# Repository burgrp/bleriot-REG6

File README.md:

# BleRiot REG6

REG6 is a six-channel solid-state-relay controller built around a
PY32F030 and PAN2110. This repository contains the KiCad hardware and a
standalone TinyGo/BleRiot module under `fw/` that exposes one integer percentage
for each channel.

## Hardware

The firmware targets a PY32F030x8 at 24 MHz. TIM1 and TIM3 generate all six
PWM outputs in hardware at a common 24 kHz frequency. Each analog path uses a
loaded two-stage 1.5 kOhm/100 nF RC ladder, whose poles are approximately
405 Hz and 2.78 kHz, followed by an LM358 with a nominal gain of 1.56. At 50%
duty, the ideal nominal filter model predicts about 12 mV peak-to-peak ripple
at 24 kHz, compared with about 2.56 V peak-to-peak at 1 kHz. The PAN2110 uses the
BleRiot three-wire SPI driver, and six chained WS2812B LEDs report channel and
link state.

| Function | MCU pin | Peripheral | Alternate function |
|---|---|---|---:|
| PWM channel 1 | PA8 | TIM1_CH1 | AF2 |
| PWM channel 2 | PA9 | TIM1_CH2 | AF2 |
| PWM channel 3 | PA10 | TIM1_CH3 | AF2 |
| PWM channel 4 | PB4 | TIM3_CH1 | AF1 |
| PWM channel 5 | PB5 | TIM3_CH2 | AF1 |
| PWM channel 6 | PF3 | TIM3_CH3 | AF13 |
| PAN2110 CSN | PF1 | GPIO | - |
| PAN2110 SCK | PA2 | GPIO, bit-banged SPI | - |
| PAN2110 DATA | PA3 | GPIO, bidirectional SPI | - |
| WS2812B data, D1-D6 | PF4 | GPIO | - |

The development inventory uses raw RF channel 37 with BLE Coded PHY S8. Its
address and XTEA key were generated offline with BleRiot's `node new` command
and are baked into the image by `node build`. This checked-in identity is public
bench provisioning; deployments must use a separately generated private
inventory identity and key.

## Registers

The `ssr` inventory instance publishes exactly these writable Registry
registers:

| Registry name | Wire tag | Registry type | Range |
|---|---:|---|---:|
| `ssr.channel.1` | 1 | int | 0..100 |
| `ssr.channel.2` | 2 | int | 0..100 |
| `ssr.channel.3` | 3 | int | 0..100 |
| `ssr.channel.4` | 4 | int | 0..100 |
| `ssr.channel.5` | 5 | int | 0..100 |
| `ssr.channel.6` | 6 | int | 0..100 |
| `ssr.watchdog` | 7 | int | 0..60 seconds |

Values are direct integer percentages on the Registry and `int32` wire protocol.
Firmware clamps assignments to 0..100, and a Registry NULL assignment clears
that channel to zero. `ssr.watchdog` is a lease counter. Positive writes arm it
for up to 60 seconds, with larger values clamped to 60; zero, negative, and NULL
writes expire it. Reads return the remaining whole seconds rounded up, or zero
at and after the monotonic deadline.
Register tags are permanent wire identities and must not be renumbered or
reused.

## Status And Safety

While BleRiot is online and the watchdog is armed, each LED represents its
matching channel level. Status indicators use the WS2812 driver's global
brightness of 128/255 (approximately 50%); normal channel colors render at half
that, approximately 25%.

The watchdog starts expired. While it is expired, channel SET requests are
acknowledged but ignored. Expiry clears all six retained channel levels and
forces both PWM timers to 0% duty. Writing a positive watchdog value re-arms
channel writes but does not restore cleared levels; every active channel needs
a fresh SET. While the radio remains online and the watchdog is expired, only
D2 blinks pure blue using the BleRiot heartbeat phase.

The node starts offline. If no valid packet has arrived, or packets stop for
more than five seconds, firmware clears all six retained levels and forces both
timers to update with 0% duty immediately. D1 then pulses orange-red for 200 ms
once per second; D2-D6 remain off. A radio initialization failure follows the
same safe output and heartbeat behavior. Reconnection does not restore old
levels: each active channel requires a fresh SET. This RF-offline indication
has priority over the online watchdog-expired indication.

## Build And Run

The module uses released BleRiot and TinyGo driver modules pinned in `fw/go.mod`.
Install TinyGo and the PY32 pyOCD pack, then run:

```sh
go -C fw test ./...
make -C fw build
make -C fw install-pack
make -C fw flash
```

Firmware v0.1.0 was built with Go 1.26.3, TinyGo commit
`f8e1f465ecae33c58772c099f9b7667c00cea9c1`, LLVM 18.1.8, pyOCD 0.44.0, and
the Puya PY32F030 CMSIS pack 1.2.8.

`make -C fw flash` builds the `ssr` inventory instance, programs it through
pyOCD, and opens RTT under reset. Confirm the intended board and probe before
using that target. To inspect generated firmware without flashing:

```sh
go -C fw run ./cmd/dev node build --name ssr
go -C fw run ./cmd/dev node gen --name ssr
```

Run the hub against a Registry service with:

```sh
go -C fw run ./cmd/dev hub --registry http://localhost:8080 --diagnostics rf
```

With the hub and Registry running, `./fw/color-test.sh` continuously renews a
five-second watchdog lease before writing the six demonstration channel levels.
Set the `REGISTRY` environment variable to use a URL other than
`http://localhost:8080`.

`make -C fw new` prints another random inventory stub; it does not update the
checked-in development identity automatically.

## Bench Validation

Perform initial validation with low-voltage loads only and no mains connected:

1. Build and flash the firmware, then verify D1 pulses orange-red and every PWM pin
   is low before the hub sends a valid packet.
2. Start the hub, arm `ssr.watchdog`, and write 0, 50, and 100 to each Registry
   channel in turn.
   Scope PA8, PA9, PA10, PB4, PB5, and PF3; expect a constant low at 0%, a
   24 kHz waveform at 50%, and a constant high at 100% duty.
3. Confirm D1-D6 track their corresponding values using the configured level
   colors, with the chain limited to approximately 25% brightness.
4. Set a short watchdog lease and all channels nonzero, then stop renewing the
   watchdog while RF stays online. Verify every PWM output goes low, all channel
   GETs return zero, and only D2 blinks pure blue. Confirm channel SETs remain
   ineffective until the watchdog is re-armed, and that re-arming alone does
   not restore outputs.
5. Set all channels nonzero, stop RF traffic for more than five seconds, and
   verify every PWM output goes low and only D1 pulses orange-red for 200 ms per
   second, even after the watchdog expires.
6. Restore RF traffic without sending SETs and confirm all outputs remain off.
   Re-arm the watchdog, send fresh channel SETs, and verify only those channels
   resume.
7. Repeat power-up with the PAN2110 unavailable or misconfigured and confirm
   all PWM outputs remain low while the offline heartbeat continues.

After logic-level validation, verify the complete channel output stages and
load polarity against the schematic before connecting actual SSR loads.

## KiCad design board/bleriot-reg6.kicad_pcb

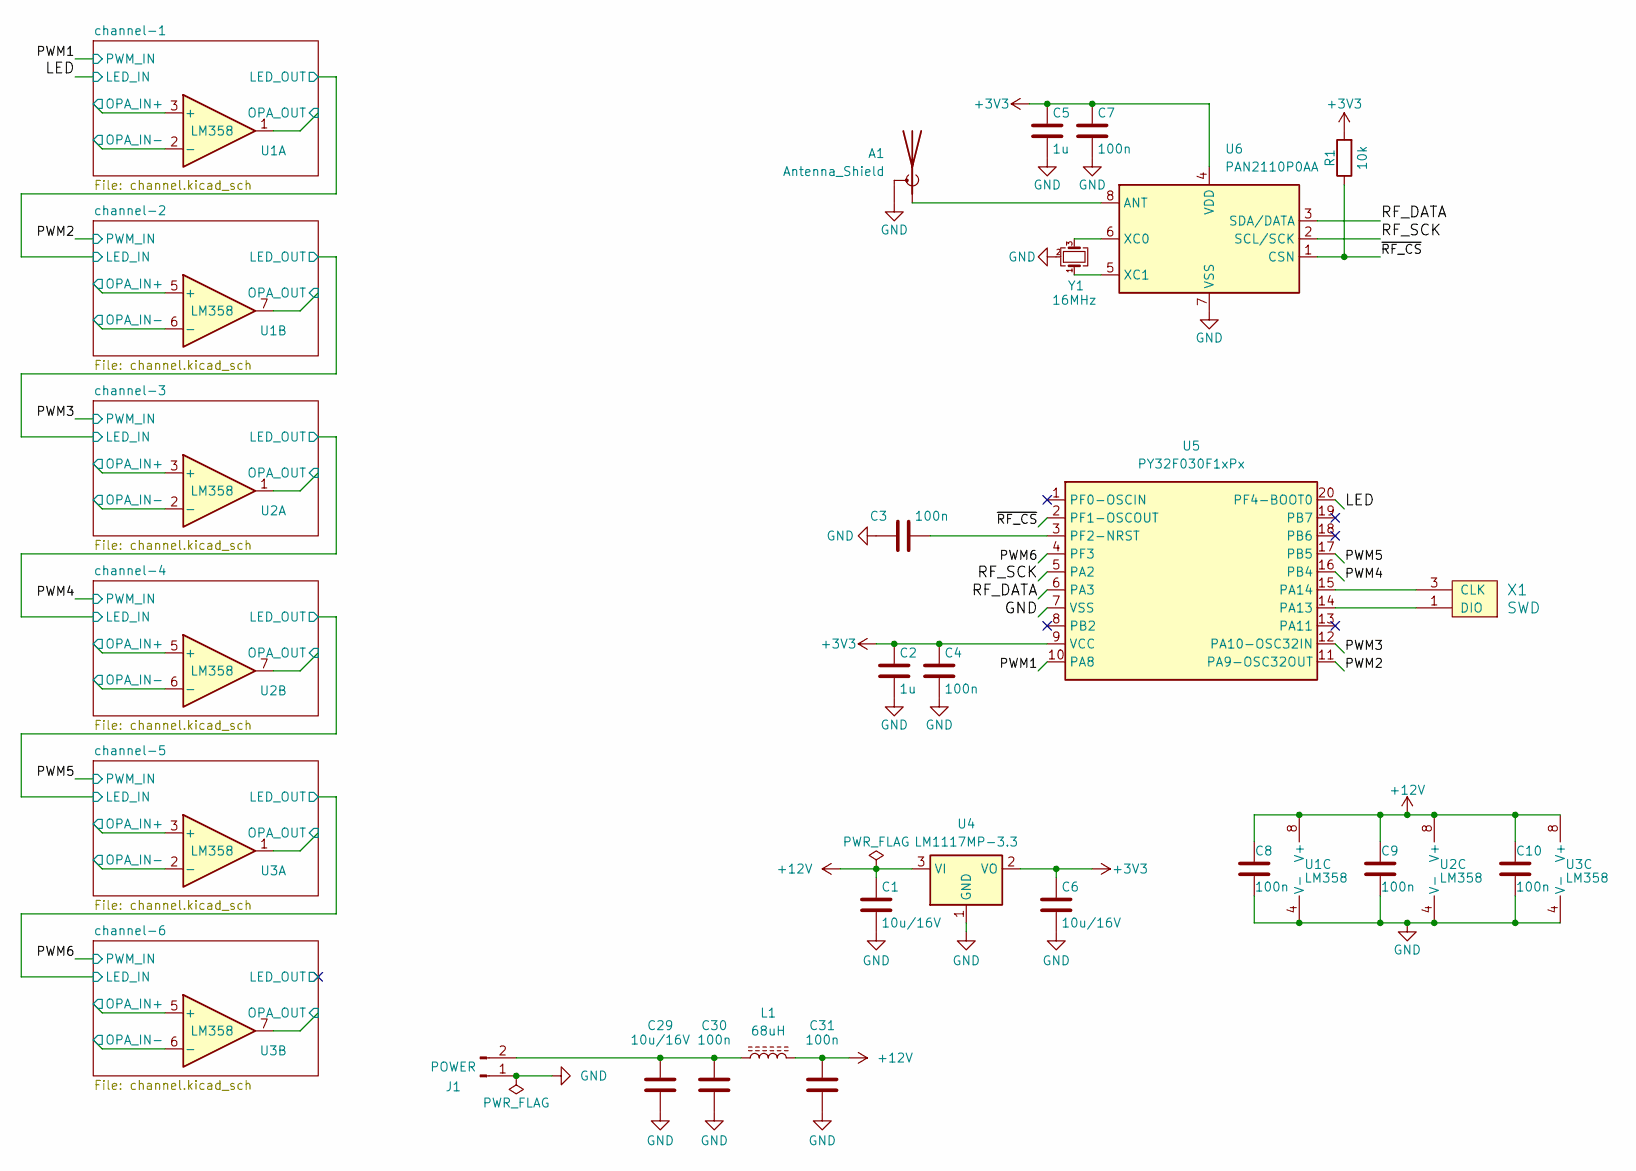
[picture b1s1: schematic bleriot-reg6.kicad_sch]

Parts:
A1: Antenna_Shield; Texas_SWRA117D_2.4GHz_Left
C1, C6, C29: 10u/16V; C_0805_2012Metric
C2, C5: 1u; C_0805_2012Metric
C3, C4, C7, C30, C31: 100n; C_0805_2012Metric
C8, C9, C10: 100n; C_0805_2012Metric_Pad1.18x1.45mm_HandSolder
J1: POWER; PhoenixContact_MSTBA_2,5_2-G_1x02_P5.00mm_Horizontal
L1: 68uH; L_Wuerth_MAPI-4020
R1: 10k; R_0805_2012Metric
U1, U2, U3: LM358; SOIC-8_3.9x4.9mm_P1.27mm
U4: LM1117MP-3.3; SOT-223-3_TabPin2
U5: PY32F030F1xPx; TSSOP-20_4.4x6.5mm_P0.65mm
U6: PAN2110P0AA; SOIC-8_3.9x4.9mm_P1.27mm
X1: SWD
Y1: 16MHz; Crystal_SMD_3225-4Pin_3.2x2.5mm

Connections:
+3V3: C2.1, C4.1, C5.1, C6.1, C7.1, R1.2, U4.2 (VO), U5.9 (VCC), U6.4 (VDD); also elsewhere on the board
+12V: C1.1, C8.1, C9.1, C10.1, C31.1, L1.2, U1.8 (V+), U2.8 (V+), U3.8 (V+), U4.3 (VI)
/LED: U5.20 (PF4-BOOT0); also elsewhere on the board
/PWM1: U5.10 (PA8); also elsewhere on the board
/PWM2: U5.11 (PA9-OSC32OUT); also elsewhere on the board
/PWM3: U5.12 (PA10-OSC32IN); also elsewhere on the board
/PWM4: U5.16 (PB4); also elsewhere on the board
/PWM5: U5.17 (PB5); also elsewhere on the board
/PWM6: U5.4 (PF3); also elsewhere on the board
/RF_DATA: U5.6 (PA3), U6.3 (SDA/DATA)
/RF_SCK: U5.5 (PA2), U6.2 (SCL/SCK)
/channel-1/OPA_IN+: U1.3 (+); also elsewhere on the board
/channel-1/OPA_IN-: U1.2 (-); also elsewhere on the board
/channel-1/OPA_OUT: U1.1; also elsewhere on the board
/channel-2/OPA_IN+: U1.5 (+); also elsewhere on the board
/channel-2/OPA_IN-: U1.6 (-); also elsewhere on the board
/channel-2/OPA_OUT: U1.7; also elsewhere on the board
/channel-3/OPA_IN+: U2.3 (+); also elsewhere on the board
/channel-3/OPA_IN-: U2.2 (-); also elsewhere on the board
/channel-3/OPA_OUT: U2.1; also elsewhere on the board
/channel-4/OPA_IN+: U2.5 (+); also elsewhere on the board
/channel-4/OPA_IN-: U2.6 (-); also elsewhere on the board
/channel-4/OPA_OUT: U2.7; also elsewhere on the board
/channel-5/OPA_IN+: U3.3 (+); also elsewhere on the board
/channel-5/OPA_IN-: U3.2 (-); also elsewhere on the board
/channel-5/OPA_OUT: U3.1; also elsewhere on the board
/channel-6/OPA_IN+: U3.5 (+); also elsewhere on the board
/channel-6/OPA_IN-: U3.6 (-); also elsewhere on the board
/channel-6/OPA_OUT: U3.7; also elsewhere on the board
/~RF_CS: R1.1, U5.2 (PF1-OSCOUT), U6.1 (CSN)
GND: A1.2 (Shield), C1.2, C2.2, C3.2, C4.2, C5.2, C6.2, C7.2, C8.2, C9.2, C10.2, C29.2, C30.2, C31.2, J1.1, U1.4 (V-), U2.4 (V-), U3.4 (V-), U4.1 (GND), U5.7 (VSS), U6.7 (VSS), X1.2 (GND), Y1.2 (G), Y1.4 (G); also elsewhere on the board
unnamed: A1.1 (A), U6.8 (ANT)
unnamed: C29.1, C30.1, J1.2, L1.1
unnamed: U5.14 (PA13), X1.1 (DIO)
unnamed: U5.15 (PA14), X1.3 (CLK)
unnamed: C3.1, U5.3 (PF2-NRST)
unnamed: U6.6 (XC0), Y1.3
unnamed: U6.5 (XC1), Y1.1

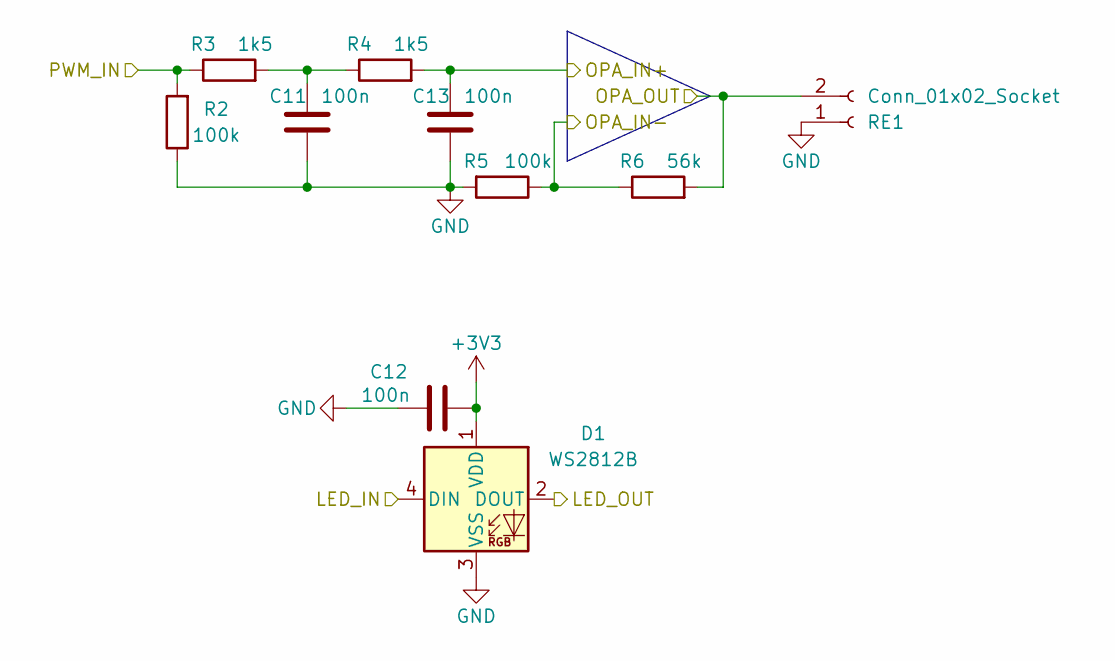
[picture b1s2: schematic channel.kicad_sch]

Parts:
C11, C12, C13: 100n; C_0805_2012Metric_Pad1.18x1.45mm_HandSolder
D1: WS2812B; LED_WS2812B_PLCC4_5.0x5.0mm_P3.2mm
R2, R5: 100k; R_0805_2012Metric_Pad1.20x1.40mm_HandSolder
R3, R4: 1k5; R_0805_2012Metric_Pad1.20x1.40mm_HandSolder
R6: 56k; R_0805_2012Metric_Pad1.20x1.40mm_HandSolder
RE1: Conn_01x02_Socket; ssr-contact

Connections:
+3V3: C12.2, D1.1 (VDD); also elsewhere on the board
/LED: D1.4 (DIN); also elsewhere on the board
/PWM1: R2.2, R3.1; also elsewhere on the board
/channel-1/LED_OUT: D1.2 (DOUT); also elsewhere on the board
/channel-1/OPA_IN+: C13.1, R4.2; also elsewhere on the board
/channel-1/OPA_IN-: R5.1, R6.1; also elsewhere on the board
/channel-1/OPA_OUT: R6.2, RE1.2; also elsewhere on the board
GND: C11.2, C12.1, C13.2, D1.3 (VSS), R2.1, R5.2, RE1.1; also elsewhere on the board
unnamed: C11.1, R3.2, R4.1

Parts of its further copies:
C14, C15, C16, C17, C18, C19, C20, C21, C22, C23, C24, C25, C26, C27, C28: 100n; C_0805_2012Metric_Pad1.18x1.45mm_HandSolder
D2, D3, D4, D5, D6: WS2812B; LED_WS2812B_PLCC4_5.0x5.0mm_P3.2mm
R7, R10, R12, R15, R17, R20, R22, R25, R27, R30: 100k; R_0805_2012Metric_Pad1.20x1.40mm_HandSolder
R8, R9, R13, R14, R18, R19, R23, R24, R28, R29: 1k5; R_0805_2012Metric_Pad1.20x1.40mm_HandSolder
R11, R16, R21, R26, R31: 56k; R_0805_2012Metric_Pad1.20x1.40mm_HandSolder
RE2, RE3, RE4, RE5, RE6: Conn_01x02_Socket; ssr-contact

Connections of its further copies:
+3V3: C15.2, C18.2, C21.2, C24.2, C27.2, D2.1 (VDD), D3.1 (VDD), D4.1 (VDD), D5.1 (VDD), D6.1 (VDD); also elsewhere on the board
/PWM2: R7.2, R8.1; also elsewhere on the board
/PWM3: R12.2, R13.1; also elsewhere on the board
/PWM4: R17.2, R18.1; also elsewhere on the board
/PWM5: R22.2, R23.1; also elsewhere on the board
/PWM6: R27.2, R28.1; also elsewhere on the board
/channel-1/LED_OUT: D2.4 (DIN); also elsewhere on the board
/channel-2/LED_OUT: D2.2 (DOUT), D3.4 (DIN)
/channel-2/OPA_IN+: C16.1, R9.2; also elsewhere on the board
/channel-2/OPA_IN-: R10.1, R11.1; also elsewhere on the board
/channel-2/OPA_OUT: R11.2, RE2.2; also elsewhere on the board
/channel-3/LED_OUT: D3.2 (DOUT), D4.4 (DIN)
/channel-3/OPA_IN+: C19.1, R14.2; also elsewhere on the board
/channel-3/OPA_IN-: R15.1, R16.1; also elsewhere on the board
/channel-3/OPA_OUT: R16.2, RE3.2; also elsewhere on the board
/channel-4/LED_OUT: D4.2 (DOUT), D5.4 (DIN)
/channel-4/OPA_IN+: C22.1, R19.2; also elsewhere on the board
/channel-4/OPA_IN-: R20.1, R21.1; also elsewhere on the board
/channel-4/OPA_OUT: R21.2, RE4.2; also elsewhere on the board
/channel-5/LED_OUT: D5.2 (DOUT), D6.4 (DIN)
/channel-5/OPA_IN+: C25.1, R24.2; also elsewhere on the board
/channel-5/OPA_IN-: R25.1, R26.1; also elsewhere on the board
/channel-5/OPA_OUT: R26.2, RE5.2; also elsewhere on the board
/channel-6/LED_OUT: D6.2 (DOUT)
/channel-6/OPA_IN+: C28.1, R29.2; also elsewhere on the board
/channel-6/OPA_IN-: R30.1, R31.1; also elsewhere on the board
/channel-6/OPA_OUT: R31.2, RE6.2; also elsewhere on the board
GND: C14.2, C15.1, C16.2, C17.2, C18.1, C19.2, C20.2, C21.1, C22.2, C23.2, C24.1, C25.2, C26.2, C27.1, C28.2, D2.3 (VSS), D3.3 (VSS), D4.3 (VSS), D5.3 (VSS), D6.3 (VSS), R7.1, R10.2, R12.1, R15.2, R17.1, R20.2, R22.1, R25.2, R27.1, R30.2, RE2.1, RE3.1, RE4.1, RE5.1, RE6.1; also elsewhere on the board
unnamed: C14.1, R8.2, R9.1
unnamed: C17.1, R13.2, R14.1
unnamed: C20.1, R18.2, R19.1
unnamed: C23.1, R23.2, R24.1
unnamed: C26.1, R28.2, R29.1

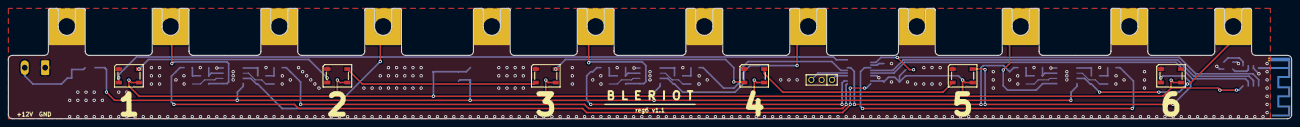
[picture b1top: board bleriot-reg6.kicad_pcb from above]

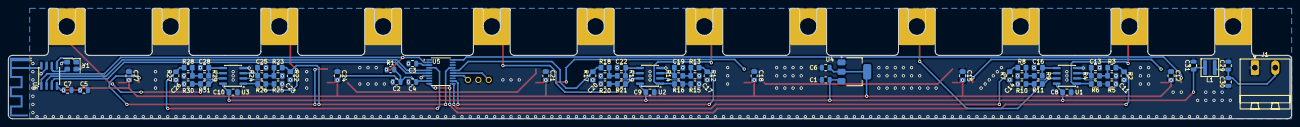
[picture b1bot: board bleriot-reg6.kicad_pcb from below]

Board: 2 copper layers, 314.0 x 27.0 mm, 85 parts (72 on the bottom side), 49 nets.
